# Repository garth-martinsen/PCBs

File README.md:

# PCBs
Schematics, PCB Layouts, Visuals

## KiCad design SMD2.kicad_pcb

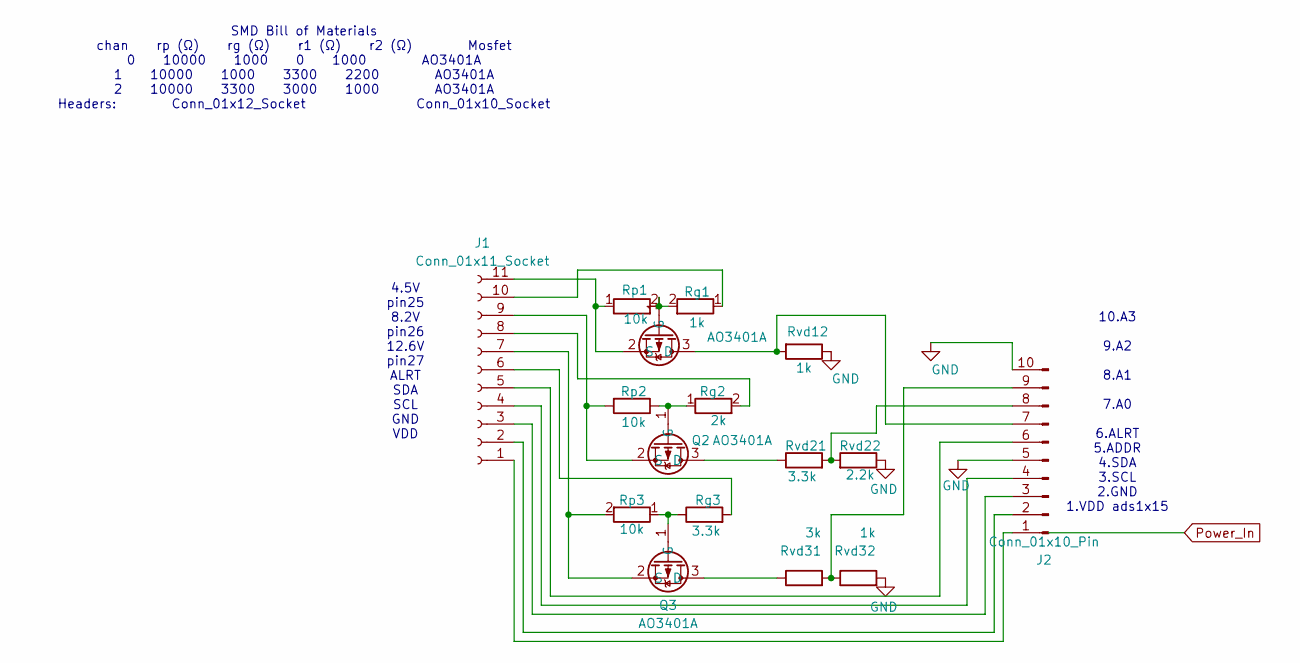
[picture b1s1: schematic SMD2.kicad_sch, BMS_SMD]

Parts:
J1: Conn_01x11_Socket; PinSocket_1x11_P2.54mm_Vertical
J2: Conn_01x10_Pin; PinSocket_1x10_P2.54mm_Vertical
Q1, Q2, Q3: AO3401A; SOT-23
Rg1: 1k; R_1210_3225Metric_Pad1.30x2.65mm_HandSolder
Rg2: 2k; R_1210_3225Metric_Pad1.30x2.65mm_HandSolder
Rg3: 3.3k; R_1210_3225Metric_Pad1.30x2.65mm_HandSolder
Rp1, Rp2, Rp3: 10k; R_1210_3225Metric_Pad1.30x2.65mm_HandSolder
Rvd12, Rvd32: 1k; R_1210_3225Metric_Pad1.30x2.65mm_HandSolder
Rvd21: 3.3k; R_1210_3225Metric_Pad1.30x2.65mm_HandSolder
Rvd22: 2.2k; R_1210_3225Metric_Pad1.30x2.65mm_HandSolder
Rvd31: 3k; R_1210_3225Metric_Pad1.30x2.65mm_HandSolder

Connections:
GND: J2.5, J2.10, Rvd12.1, Rvd22.1, Rvd32.2
unnamed: J1.1, J2.1
unnamed: J1.2, J2.2
unnamed: J1.3, J2.3
unnamed: J1.4, J2.4
unnamed: J1.5, J2.6
unnamed: J1.6, Rg3.2
unnamed: J1.7, Q3.2 (S), Rp3.2
unnamed: J1.8, Rg2.2
unnamed: J1.9, Q2.2 (S), Rp2.2
unnamed: J1.10, Rg1.1
unnamed: J1.11, Q1.2 (S), Rp1.1
unnamed: J2.7, Q1.3 (D), Rvd12.2
unnamed: J2.8, Rvd21.2, Rvd22.2
unnamed: J2.9, Rvd31.2, Rvd32.1
unnamed: Q1.1 (G), Rg1.2, Rp1.2
unnamed: Q2.3 (D), Rvd21.1
unnamed: Q2.1 (G), Rg2.1, Rp2.1
unnamed: Q3.3 (D), Rvd31.1
unnamed: Q3.1 (G), Rg3.1, Rp3.1

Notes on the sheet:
SMD Bill of Materials chan rp (Ω) rg (Ω) r1 (Ω) r2 (Ω) Mosfet 0 10000 1000 0 1000 AO3401A 1 10000 1000 3300 2200 AO3401A 2 10000 3300 3000 1000 AO3401A Headers: Conn_01x12_Socket Conn_01x10_Socket
10.A3 9.A2 8.A1 7.A0 6.ALRT 5.ADDR 4.SDA 3.SCL 2.GND 1.VDD ads1x15
4.5V pin25 8.2V pin26 12.6V pin27 ALRT SDA SCL GND VDD

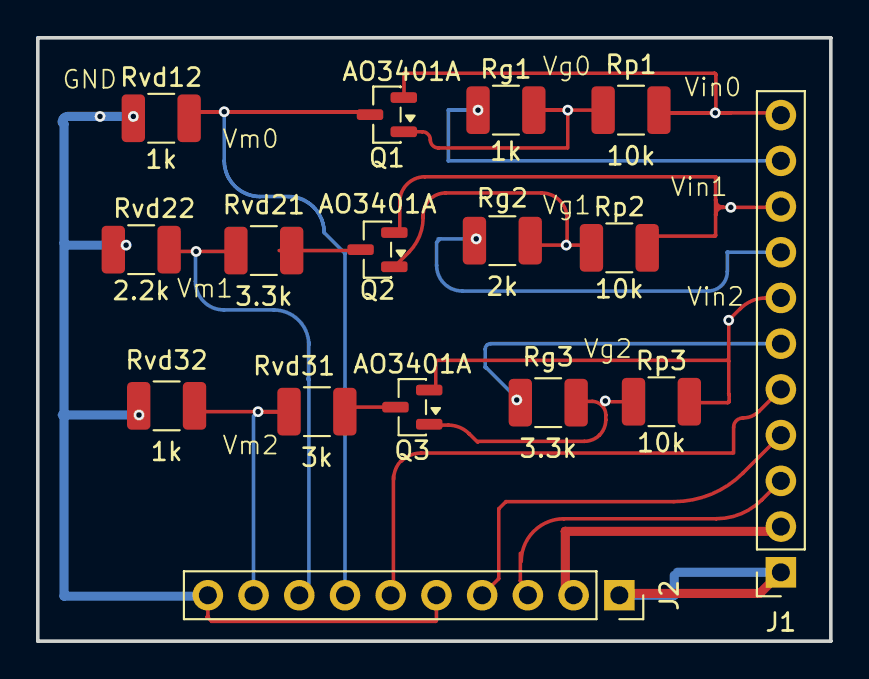
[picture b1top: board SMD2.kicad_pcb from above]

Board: 2 copper layers, 44.1 x 33.5 mm, 16 parts (0 on the bottom side), 20 nets.

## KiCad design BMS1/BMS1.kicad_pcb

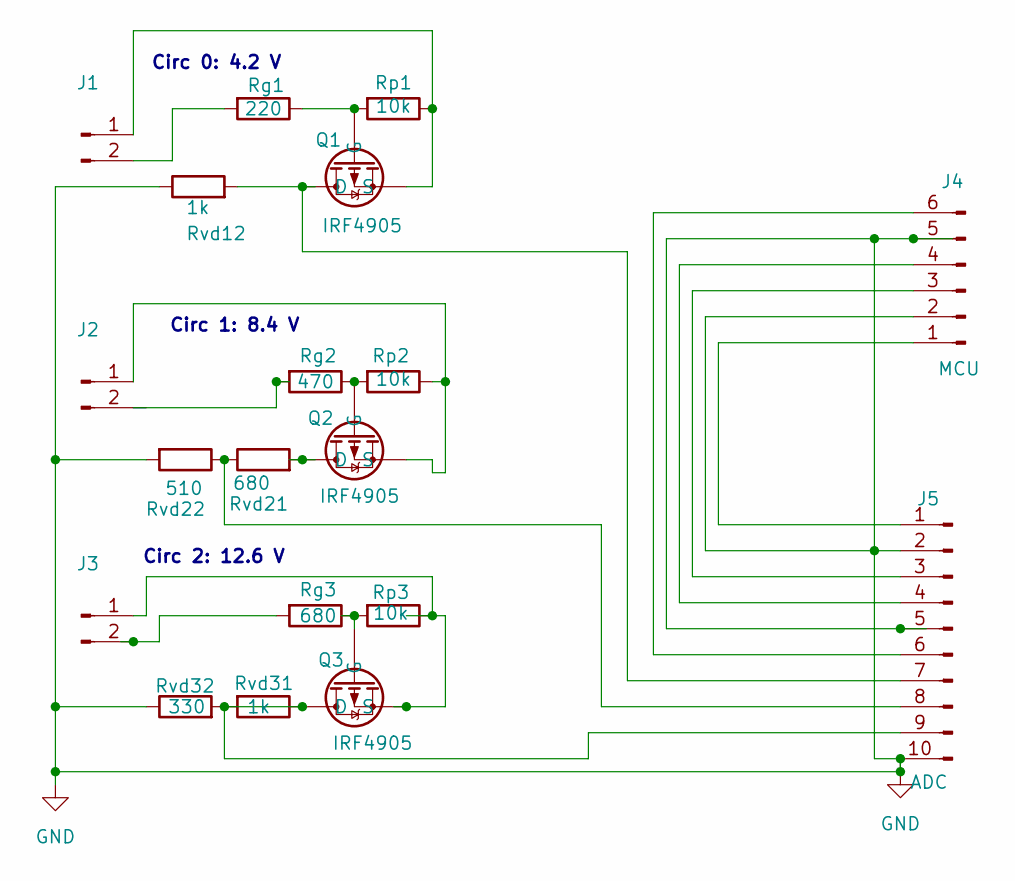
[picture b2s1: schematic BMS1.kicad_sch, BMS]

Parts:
J1: 4.2V; PinSocket_1x02_P2.54mm_Vertical
J2: 8.4V; PinSocket_1x02_P2.54mm_Vertical
J3: 12.6V; PinSocket_1x02_P2.54mm_Vertical
J4: MCU; PinSocket_1x06_P2.54mm_Vertical
J5: ADC; PinSocket_1x10_P2.54mm_Vertical
Q1, Q2, Q3: IRF4905; TO-220-3_Vertical
Rg1: 220; R_Axial_DIN0207_L6.3mm_D2.5mm_P7.62mm_Horizontal
Rg2: 470; R_Axial_DIN0207_L6.3mm_D2.5mm_P7.62mm_Horizontal
Rg3: 680; R_Axial_DIN0207_L6.3mm_D2.5mm_P7.62mm_Horizontal
Rp1, Rp2, Rp3: 10k; R_Axial_DIN0207_L6.3mm_D2.5mm_P7.62mm_Horizontal
Rvd12, Rvd31: 1k; R_Axial_DIN0207_L6.3mm_D2.5mm_P7.62mm_Horizontal
Rvd21: 680; R_Axial_DIN0207_L6.3mm_D2.5mm_P7.62mm_Horizontal
Rvd22: 510; R_Axial_DIN0207_L6.3mm_D2.5mm_P7.62mm_Horizontal
Rvd32: 330; R_Axial_DIN0207_L6.3mm_D2.5mm_P7.62mm_Horizontal

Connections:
GND: J4.2, J4.5, J5.2, J5.5, J5.10, Rvd12.1, Rvd22.2, Rvd32.1
unnamed: J1.1, Q1.3 (S), Rp1.1
unnamed: J1.2, Rg1.2
unnamed: J2.1, Q2.3 (S), Rp2.1
unnamed: J2.2, Rg2.2
unnamed: J3.1, Q3.3 (S), Rp3.1
unnamed: J3.2, Rg3.2
unnamed: J4.1, J5.1
unnamed: J4.3, J5.3
unnamed: J4.4, J5.4
unnamed: J4.6, J5.6
unnamed: J5.7, Q1.2 (D), Rvd12.2
unnamed: J5.8, Rvd21.1, Rvd22.1
unnamed: J5.9, Q3.2 (D), Rvd31.1, Rvd31.2, Rvd32.2
unnamed: Q1.1 (G), Rg1.1, Rp1.2
unnamed: Q2.2 (D), Rvd21.2
unnamed: Q2.1 (G), Rg2.1, Rp2.2
unnamed: Q3.1 (G), Rg3.1, Rp3.2

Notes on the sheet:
Circ 2: 12.6 V
Circ 1: 8.4 V
Circ 0: 4.2 V

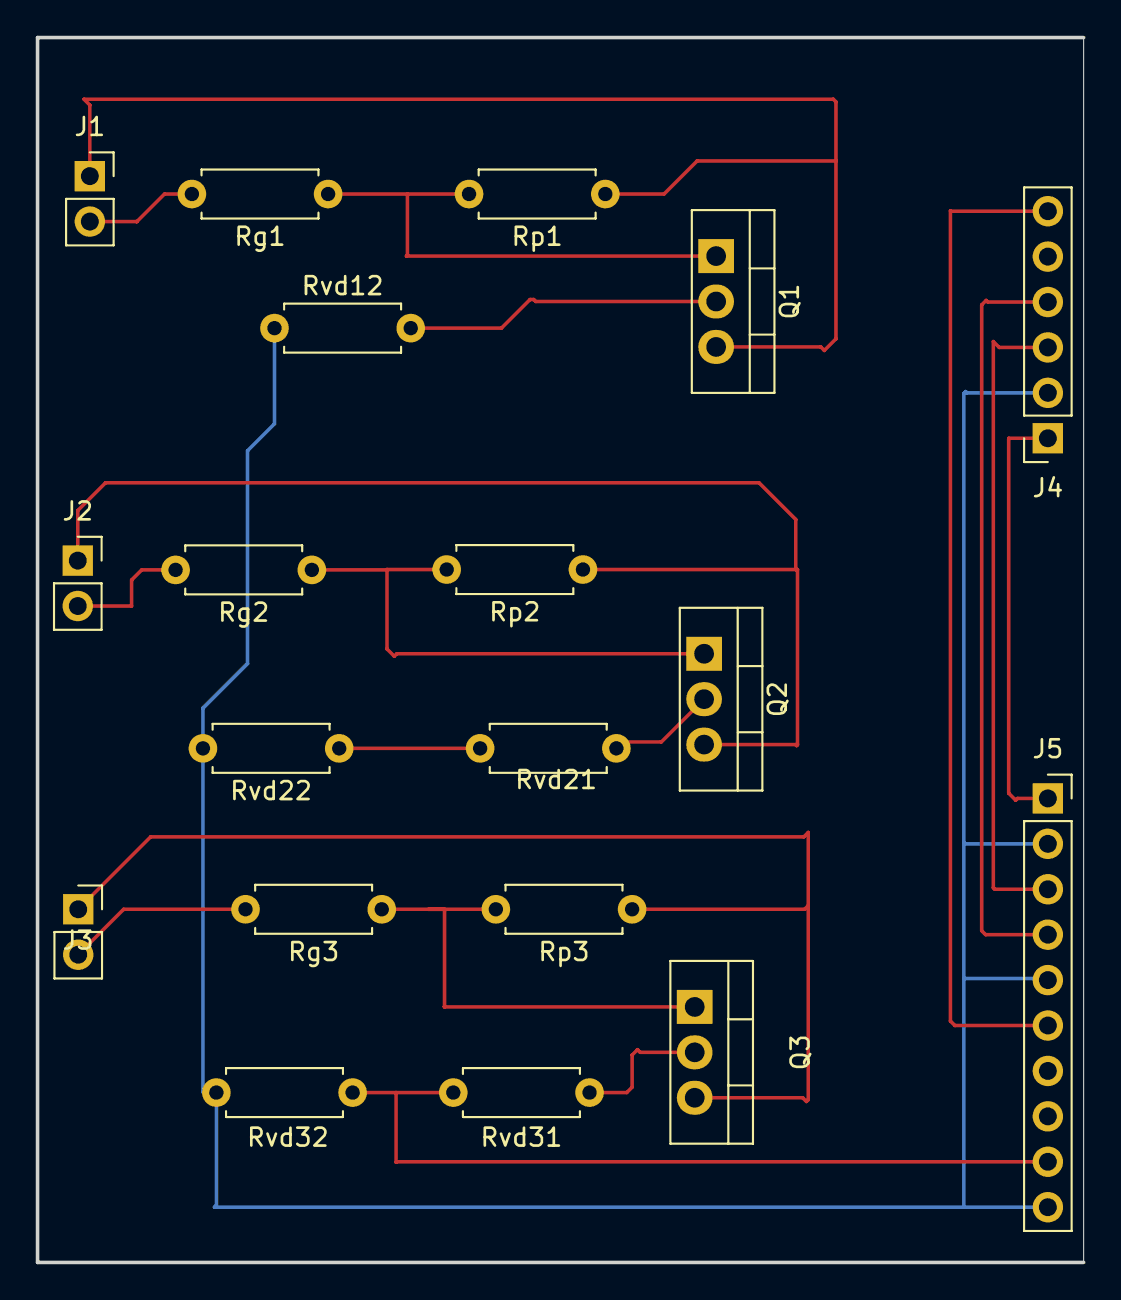
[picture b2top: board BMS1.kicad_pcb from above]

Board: 2 copper layers, 58.5 x 68.5 mm, 19 parts (0 on the bottom side), 18 nets.

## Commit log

2026-01-03 Front and Back images (png) of the PCB for BMS 1/2/2026
2026-01-03 Front of PCB for BMS1 on 1/2/2026
2026-01-03 Schematic for BMS1 1/2/2026
2026-01-03 .gitignore file
2026-01-03 Removed file
2026-01-03 Removed file.
2026-01-03 Removed
2026-02-11 Surface Mount Components for BMS project.
2026-02-11 Schematic diagram for SMD PCB BMS.

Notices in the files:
BMS1.kicad_sch:
creativecommons.com
Licence: TBD
